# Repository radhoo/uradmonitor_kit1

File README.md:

# uradmonitor_kit1

A hackable open source DIY Geiger Counter Kit with a network interface to the
uRADMonitor servers

Project page: 
[http://www.uradmonitor.com/open-source-uradmonitor-kit1/](http://www.uradmonitor.com/open-source-uradmonitor-kit1/)

See the [wiki](https://github.com/radhoo/uradmonitor_kit1/wiki) for more
details.

My fork has some bug fixes and extra features:

- optional BME280 for temperature, pressure and humidity monitoring
- max/min/mean statistics, reported in JSON over ethernet
- sends CSV out the serial port every 10 seconds; the idea is to use an 
  [AdaLogger](https://github.com/ec1oud/adalogger-serial) to log to an SD card
  for mobile surveys
- design for a 3D printed case, with a slot for an old Nokia battery (like
  BP-3L BP-4L BV-4D or any with the same width and pinout).  I used diode legs
  for contacts, which were a bit fiddly to mount but ended up working well
  enough.  One diode is needed anyway for protection, and to drop from 3.7-4V
  down to 3-3.3V.  I didn't bother with a power switch; inserting the battery
  turns it on.

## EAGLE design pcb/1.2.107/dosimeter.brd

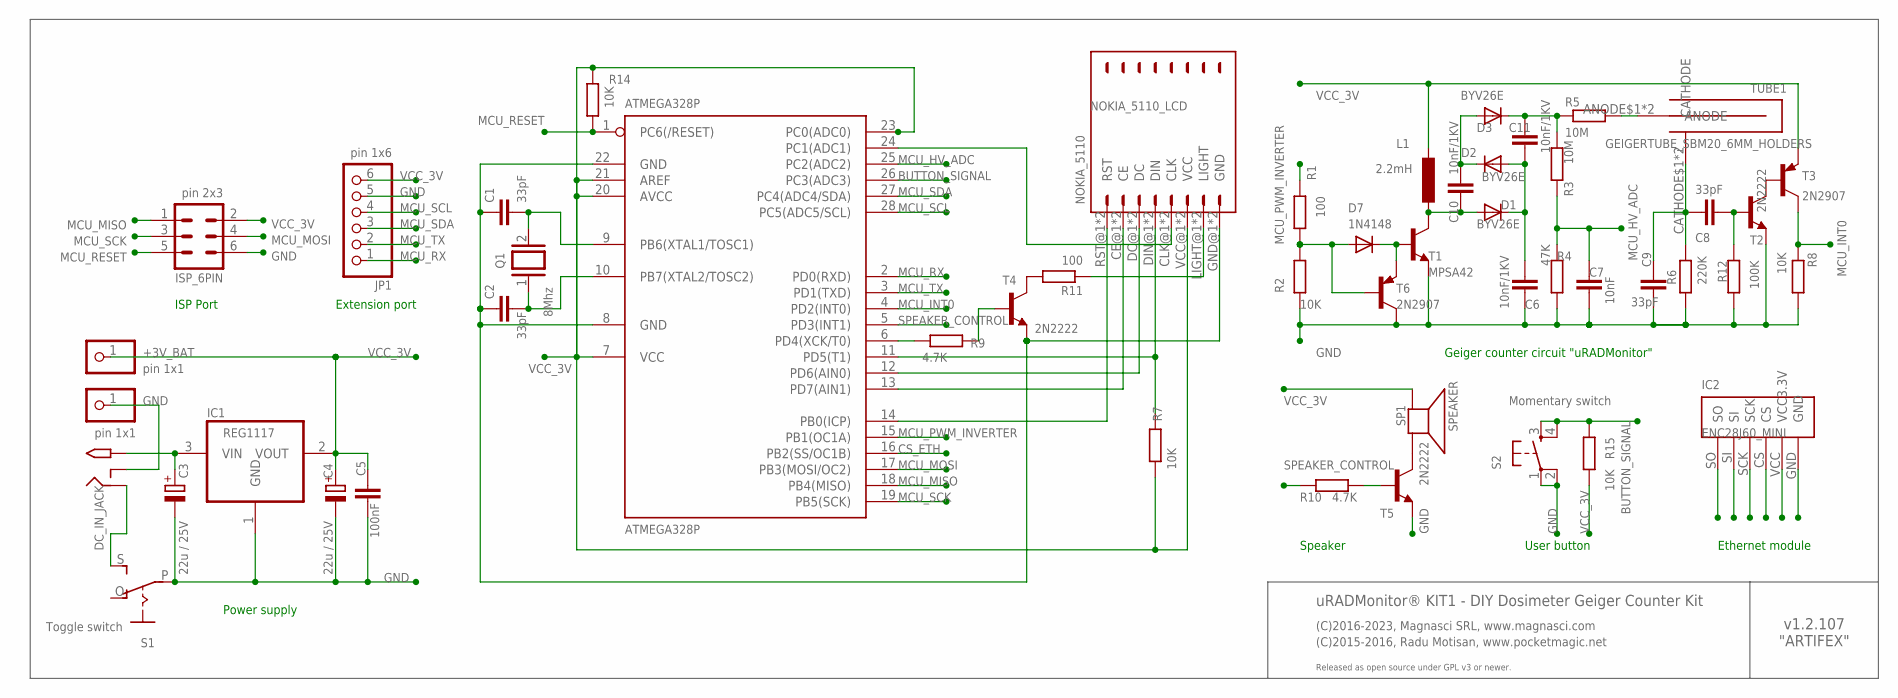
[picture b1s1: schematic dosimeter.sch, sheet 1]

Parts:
+3V_BAT: pin 1x1; 1X01
ATMEGA328P: ATMEGA328P; DIL28-3
C1, C2, C8, C9: 33pF; C2.5-2
C3, C4: 22u / 25V; TT2D4L
C5: 100nF; C2.5-2
C6, C10, C11: 10nF/1KV; C5B3
C7: 10nF; C2.5-2
D1, D2, D3: BYV26E; DO41-7.6
D7: 1N4148; D-5
DC_IN_JACK: DC IN JACK; PJ-102A
GND: pin 1x1; 1X01
IC1: REG1117; SOT223
IC2: ENC28J60_MINI
ISP_6PIN: pin 2x3; MA03-2
JP1: pin 1x6; 1X06-CLEAN
L1: 2.2mH; 0207/10
NOKIA_5110: NOKIA_5110_LCD; NOKIA5110
Q1: 8Mhz; QS
R1, R11: 100; 0204/7
R2, R7, R8, R14, R15: 10K; 0204/7
R3, R5: 10M; 0204/7
R4: 47K; 0204/7
R6: 220K; 0204/7
R9, R10: 4.7K; 0204/7
R12: 100K; 0204/7
S1: Toggle switch; EG1218
S2: Momentary switch; TACTILE-PTH
SP1: SPEAKER; AL60P
T1: MPSA42; TO92-EBC-OVAL
T2, T4, T5: 2N2222; TO92-EBC
T3, T6: 2N2907; TO92-EBC-OVAL
TUBE1: GEIGERTUBE_SBM20_6MM_HOLDERS

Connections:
BUTTON_SIGNAL: ATMEGA328P.26 (PC3(ADC3)), R15.1, S2.3, S2.4
CS_ETH: ATMEGA328P.16 (PB2(SS/OC1B)), IC2.CS
GND: ATMEGA328P.8 (GND), ATMEGA328P.22 (GND), C1.1, C2.1, C3.-, C4.-, C5.1, C6.2, C7.1, C9.2, IC1.1 (GND), IC2.GND, ISP_6PIN.6, JP1.5, NOKIA_5110.GND@1 (GND), NOKIA_5110.GND@2 (GND), R2.1, R4.2, R6.1, R8.2, R12.2, S1.P, S2.1, S2.2, T1.E, T2.E, T4.E, T5.E, T6.C
MCU_HV_ADC: ATMEGA328P.25 (PC2(ADC2)), C7.2, R3.1, R4.1
MCU_INT0: ATMEGA328P.4 (PD2(INT0)), R8.1, T3.C
MCU_MISO: ATMEGA328P.18 (PB4(MISO)), IC2.SO, ISP_6PIN.1
MCU_MOSI: ATMEGA328P.17 (PB3(MOSI/OC2)), IC2.SI, ISP_6PIN.4
MCU_PWM_INVERTER: ATMEGA328P.15 (PB1(OC1A)), R1.1
MCU_RESET: ATMEGA328P.1 (PC6(/RESET)), ISP_6PIN.5, R14.1
MCU_RX: ATMEGA328P.2 (PD0(RXD)), JP1.1
MCU_SCK: ATMEGA328P.19 (PB5(SCK)), IC2.SCK, ISP_6PIN.3
MCU_SCL: ATMEGA328P.28 (PC5(ADC5/SCL)), JP1.4
MCU_SDA: ATMEGA328P.27 (PC4(ADC4/SDA)), JP1.3
MCU_TX: ATMEGA328P.3 (PD1(TXD)), JP1.2
unnamed: ATMEGA328P.9 (PB6(XTAL1/TOSC1)), C1.2, Q1.2
unnamed: ATMEGA328P.10 (PB7(XTAL2/TOSC2)), C2.2, Q1.1
unnamed: R11.2, T4.C
unnamed: R5.2, TUBE1.ANODE$1 (ANODE), TUBE1.ANODE$2 (ANODE)
unnamed: R9.2, T4.B
unnamed: NOKIA_5110.LIGHT@1 (LIGHT), NOKIA_5110.LIGHT@2 (LIGHT), R11.1
unnamed: C10.2, D1.A, L1.2, T1.C
unnamed: ATMEGA328P.24 (PC1(ADC1)), NOKIA_5110.CLK@1 (CLK), NOKIA_5110.CLK@2 (CLK)
unnamed: DC_IN_JACK.RING, S1.S
unnamed: C10.1, D2.C, D3.A
unnamed: DC_IN_JACK.RING_SW, GND.1
unnamed: ATMEGA328P.11 (PD5(T1)), NOKIA_5110.DIN@1 (DIN), NOKIA_5110.DIN@2 (DIN), R7.2
unnamed: ATMEGA328P.12 (PD6(AIN0)), NOKIA_5110.DC@1 (DC), NOKIA_5110.DC@2 (DC)
unnamed: ATMEGA328P.13 (PD7(AIN1)), NOKIA_5110.CE@1 (CE), NOKIA_5110.CE@2 (CE)
unnamed: ATMEGA328P.14 (PB0(ICP)), NOKIA_5110.RST@1 (RST), NOKIA_5110.RST@2 (RST)
unnamed: D7.A, R1.2, R2.2, T6.B
unnamed: C3.+, DC_IN_JACK.TIP, IC1.3 (VIN)
unnamed: C6.1, C11.2, D1.C, D2.A
unnamed: C11.1, D3.C, R3.2, R5.1
unnamed: ATMEGA328P.6 (PD4(XCK/T0)), R9.1
unnamed: SP1.2 (-), T5.C
unnamed: R10.2, T5.B
unnamed: C8.2, C9.1, R6.2, TUBE1.CATHODE$1 (CATHODE), TUBE1.CATHODE$2 (CATHODE)
unnamed: C8.1, R12.1, T2.B
unnamed: T2.C, T3.B
unnamed: D7.C, T1.B, T6.E
SPEAKER_CONTROL: ATMEGA328P.5 (PD3(INT1)), R10.1
VCC_3V: +3V_BAT.1, ATMEGA328P.7 (VCC), ATMEGA328P.20 (AVCC), ATMEGA328P.21 (AREF), ATMEGA328P.23 (PC0(ADC0)), C4.+, C5.2, IC1.2 (VOUT), IC2.VCC (VCC3.3V), ISP_6PIN.2, JP1.6, L1.1, NOKIA_5110.VCC@1 (VCC), NOKIA_5110.VCC@2 (VCC), R7.1, R14.2, R15.2, SP1.1 (+), T3.E

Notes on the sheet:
uRADMonitor® KIT1 - DIY Dosimeter Geiger Counter Kit
Power supply
Speaker
User button
Geiger counter circuit "uRADMonitor"
Extension port
ISP Port
Ethernet module
(C)2015-2016, Radu Motisan, www.pocketmagic.net
Released as open source under GPL v3 or newer.
v1.2.107 "ARTIFEX"
(C)2016-2023, Magnasci SRL, www.magnasci.com

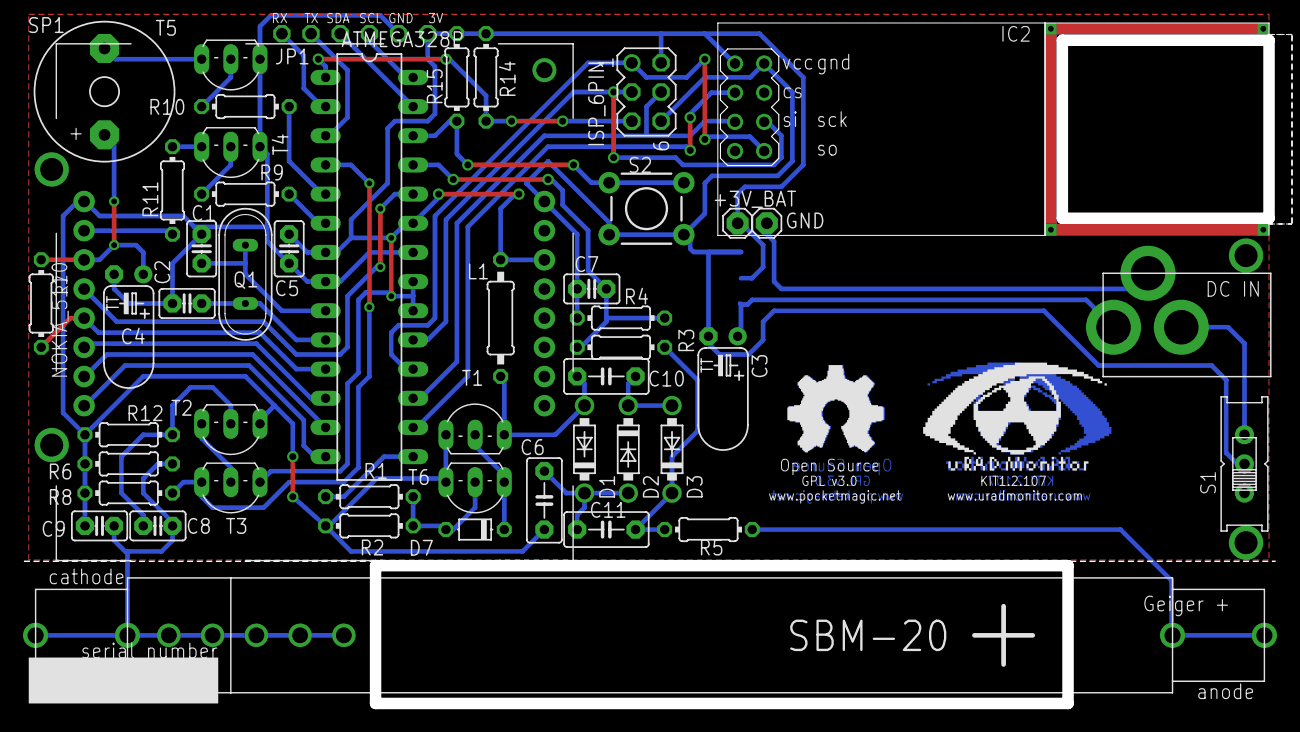
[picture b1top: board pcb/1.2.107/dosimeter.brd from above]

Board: 2 copper layers, 108.1 x 57.8 mm, 50 parts (1 on the bottom side), 42 nets.

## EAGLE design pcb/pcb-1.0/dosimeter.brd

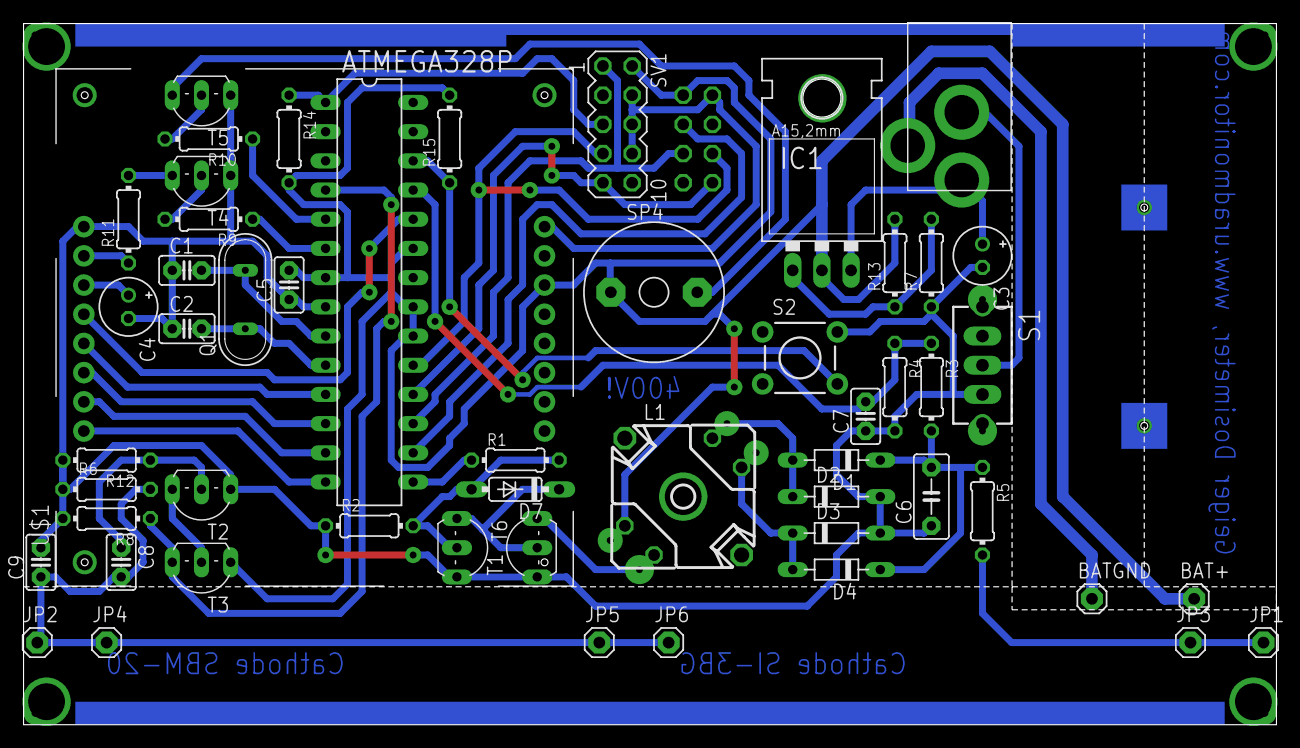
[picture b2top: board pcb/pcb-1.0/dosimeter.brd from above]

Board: 2 copper layers, 109.0 x 61.0 mm, 54 parts (1 on the bottom side), 39 nets.

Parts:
ATMEGA328P: ATMEGA328P; DIL28-3
BAT+: 1X01
BATGND: 1X01
C1, C2, C8: 33p; C2.5-2
C3: 22uF 50V; E2-5
C4: 47uF 16V; E2-5
C5: 100nF; C2.5-2
C6: 100nF; C5B3
C7: 15nF; C2.5-2
C9: 33pF; C2.5-2
D1, D2, D3, D4: BYV26E; D-7.5
D7: 1N4148DO35-7; DO35-7
IC1: 317TL
JP1, JP2, JP3, JP4, JP5, JP6: 1X01
L1: RM5-4
Q1: 8Mhz; QS
R1, R9, R10, R11: 100; 0204/7
R2, R8, R14, R15: 10K; 0204/7
R3: 10M 1%; 0204/7
R4: 47K 1%; 0204/7
R5: 10M; 0204/7
R6: 220K; 0204/7
R7: 1.4K; 0204/7
R12: 100K; 0204/7
R13: 1K; 0204/7
S1: TL32YO; TL3XYO
S2: TACTILE-PTH
SP4: SPEAKER/AL60P; AL60P
SV1: isp; MA05-2
SV3: ethernet; MA04-2
T1, T2: 2N2222; TO92-EBC-OVAL
T3, T6: 2N2907; TO92-EBC-OVAL
T4, T5: 2n2222; TO92-EBC
U$1: NOKIA5110
U$2: 2.1MMJACKTHM; PJ-102A

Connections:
unnamed: ATMEGA328P.9, C1.2, Q1.2
unnamed: ATMEGA328P.10, C2.2, Q1.1
unnamed: R11.2, T4.C
unnamed: ATMEGA328P.17, SV1.1, SV3.3
unnamed: ATMEGA328P.16, SV3.5
unnamed: ATMEGA328P.18, SV1.9, SV3.2
unnamed: R9.2, T4.B
unnamed: ATMEGA328P.19, SV1.7, SV3.4
unnamed: R11.1, U$1.B7, U$1.T7
unnamed: ATMEGA328P.1, R14.1, SV1.5
unnamed: ATMEGA328P.8, ATMEGA328P.22, C1.1, C2.1, C3.-, C4.-, C5.1, C6.1, C7.1, C9.2, D2.A, D3.A, R2.1, R4.2, R6.1, R7.1, R8.2, R12.2, S1.3, S2.2, SV1.4, SV1.6, SV1.8, SV3.8, T1.E, T2.E, T4.E, T5.E, T6.C, U$1.B8, U$1.T8
unnamed: ATMEGA328P.24, U$1.B5, U$1.T5
unnamed: ATMEGA328P.26, R15.1, S2.4
unnamed: S1.2, U$2.RING
unnamed: JP1.1, JP3.1, R5.2
unnamed: BATGND.1, U$2.RING_SW
unnamed: ATMEGA328P.11, U$1.B4, U$1.T4
unnamed: ATMEGA328P.12, U$1.B3, U$1.T3
unnamed: ATMEGA328P.13, U$1.B2, U$1.T2
unnamed: ATMEGA328P.14, U$1.B1, U$1.T1
unnamed: ATMEGA328P.7, ATMEGA328P.20, ATMEGA328P.21, ATMEGA328P.23, BAT+.1, C4.+, C5.2, IC1.2, L1.6, R13.2, R14.2, R15.2, SP4.1, SV1.2, SV3.7, T3.E, U$1.B6, U$1.T6
unnamed: ATMEGA328P.15, R1.1
unnamed: D7.A, R1.2, R2.2, T6.B
unnamed: C3.+, IC1.3, U$2.TIP
unnamed: L1.2, T1.C
unnamed: D3.C, D4.A, L1.3
unnamed: D1.A, D2.C, L1.5
unnamed: ATMEGA328P.6, R9.1
unnamed: C6.2, D1.C, D4.C, R3.2, R5.1
unnamed: SP4.2, T5.C
unnamed: R10.2, T5.B
unnamed: ATMEGA328P.5, R10.1
unnamed: IC1.1, R7.2, R13.1
unnamed: C8.2, C9.1, JP2.1, JP4.1, JP5.1, JP6.1, R6.2
unnamed: ATMEGA328P.25, C7.2, R3.1, R4.1
unnamed: C8.1, R12.1, T2.B
unnamed: T2.C, T3.B
unnamed: ATMEGA328P.4, R8.1, T3.C
unnamed: D7.C, T1.B, T6.E

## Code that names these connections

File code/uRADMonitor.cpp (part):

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/************************************************************************************************************************************************/
char				buffer[120]		= { 0 };		// general purpose buffer

DigitalPin			speaker(&PORTD, PD3),			// used to create digital pulse on radiation event
					backlight(&PORTD, PD4),			// used to toggle LCD light on and off
					button(&PORTC, PC3, DigitalPin::INPUT), // user button, configured as input pin
					lcdReset(&PORTB, PB0), 			// lcd rst pin
					lcdCE(&PORTD, PD7),				// lcd CE pin
					lcdDC(&PORTD, PD6), 			// lcd DC pin
					lcdDATA(&PORTD, PD5), 			// lcd data pin
					lcdCLK(&PORTC, PC1);			// lcd CLK pin
LCD_5110			lcd(&lcdReset, &lcdCE, &lcdDC, &lcdDATA, &lcdCLK, &backlight);	// handle the LCD ops for drawing content onscreen
TimeCounter			time;
Data				data(&time);
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// timer0 overflow interrupt   event to be executed every  2.048ms here when on 8MHz, and every 1.024ms for 16MHz */
ISR (TIMER0_OVF_vect) { time.TimerEvent(); }

// int0 interrupt handler, triggered each time a rising edge is detected on INT0, which on a ATmega8 is PD2
// we have a top limit of 2^32-1 pulses. We don't go over it.
ISR (INT0_vect) {
	geigerPulses++; // count this pulse
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	// configure device ID and MAC
	data.setDeviceID_Mac(((uint32_t) DEV_CLASS << 24) | ((uint32_t) deviceNumber & 0x00FFFFFF));

	// 2.CONFIGURE INTERRUPT INT0  to count pulses from Geiger Counter, connected on PIN PD2
	EICRA |= _BV(ISC00) | _BV(ISC01);// Configure INT0 to trigger on RISING EDGE - Instead of MCUCR, you need to use EICRA. mega8:MCUCR , mega328p: EICR
	EIMSK |= _BV(INT0); // Configure INT0 to fire interrupts - Instead of GICR, you need to use EIMSK mega8:GICR , mega328p: EIMSK

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
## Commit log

2015-10-04 uradmonitor KIT 1.1 update
2015-10-04 added BOM for PCB 1.1
2016-04-06 added hw pcb-1.1.103
2016-04-06 structured pcb in separate folder
2016-10-12 full open source release v1.2.105 under GPL v3
2016-10-12 bme280 sensor disabled by default, see config.h
2016-10-12 added BOM for 1.2.105 pcb
2017-01-07 add Makefile, and make it build on Linux
    Filenames are case-sensitive
2017-01-07 clean up trailing whitespace
    My editor does this automatically, so I end up with lots of noisy diffs
    if this isn't done in advance.
2017-01-07 LCD font: provide the missing last byte of the U character
2017-01-07 can disable backlight timeout by setting to 0
2017-01-07 fix some warnings
2017-01-07 format dose with fixed width
    This prevents wrapping the display incorrectly.
2017-01-07 BME280: don't zero-prefix the temperature or humidity
    Having a space in case the temperature or humidity is less than
    3 digits makes it easier to read.
2017-01-07 BME280: convert temperature to floating point accurately
    fix from http://www.uradmonitor.com/topic/floating-point-temperature-in-bme280-cpp/
2017-02-04 Adding PSTR macro to jsonKeyFind() call in callback_browser() needs _P string functions to be used here
2017-02-05 Remove whitespaces
2017-02-05 Include pgmspace.h as we are using _P string functions and PSTR macros
2017-02-05 Fix missing humidity value on local webserver
2017-02-06 Transmit tube type as suggested by Radu
2017-02-07 Add whitespaces because of compiler warnings
2017-02-08 Makefile: add -Wl,-relax linker option
    This makes the code a little smaller. If I build with avr-gcc 4.8.2
    on Ubuntu, it otherwise ends up just a little too large to fit in flash.
2017-02-14 pass all compile flags to the linker as well; generate a map file
    http://stackoverflow.com/questions/20356871/avr-gcc-destructive-optimizations
    says it's a good idea.
2017-02-14 strip unused functions to save space
    http://stackoverflow.com/questions/6687630/how-to-remove-unused-c-c-symbols-with-gcc-and-ld
2017-02-14 use avr-size to show memory usage after compilation
    I want to add a ring buffer but memory is tight.
2017-02-14 scavenge some memory
    even more PSTR; bit packing of some variables
2017-02-14 use the preprocessor rather than switch statements to deal with tube type
    A switch statement might take memory if the compiler generates a jump table:
    http://thegaragelab.com/conserving-memory-on-an-avr/
    (although it seems to me that it doesn't, with avr-gcc 4.8, at least).
    The tube type will not change at runtime; we only need a multiplier
    constant, and the name as a string for concatenation. The compiler
    can do string concatenation too, so there's no reason to use
2017-02-23 calculate some statistics: max, min, mean
    For this we need a ring buffer to remember at least a few samples.
    If we want to have a line graph later, we'll need to remember even more.
    But more urgently the idea is to find the outliers, which requires
    comparing against the mean... this isn't done yet.
2017-02-23 add stats to JSON response
    cpmMin, cpmMax, cpmAverage
2017-02-24 convert RingBuf to a C++ template class
    We'll soon need other buffers storing other types.
2017-07-29 bug/typo fixed
2017-08-05 issues fixed, sw 123, hw 1.2.106
2017-08-05 added missing humidity for bme280 in mini webserver
2018-04-12 added SBT10A
2018-04-12 merged and removed ds store files
2019-01-12 send status out over serial port every 10 seconds
    This makes possible logging in the field with an Adalogger or some such.
2022-02-26 update README; add programming setup pics
    My memory sucks; if I hadn't left the programmer attached to the device,
    I'd have forgotten how to connect it for programming, and that I even
    had a 3.3V programmer in the first place, and what kind.
2022-03-01 add pic of battery slot
2022-09-22 Update expProtocol.h
    Update + suggestion to the exProtocol as discussed on the uRadmonitor forum.
    https://www.uradmonitor.com/topic/expprotocol-extra-extended-codes/
2023-08-06 HW 1.2.107

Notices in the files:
code/uRADMonitor.cpp:
License:		GPL v3
Copyright 2013 by Radu Motisan, radu.motisan@gmail.com
Copyright 2016 by Magnasci SRL, www.magnasci.com
This program is free software: you can redistribute it and/or modify
it under the terms of the GNU General Public License as published by
the Free Software Foundation, either version 3 of the License, or
(at your option) any later version.
pcb-1.1.103/dosimeter.sch:
DIY Dosimeter Geiger Counter Kit, (C)2015-2016 Radu Motisan www.pocketmagic.net  . Released as open source under GPL v2
